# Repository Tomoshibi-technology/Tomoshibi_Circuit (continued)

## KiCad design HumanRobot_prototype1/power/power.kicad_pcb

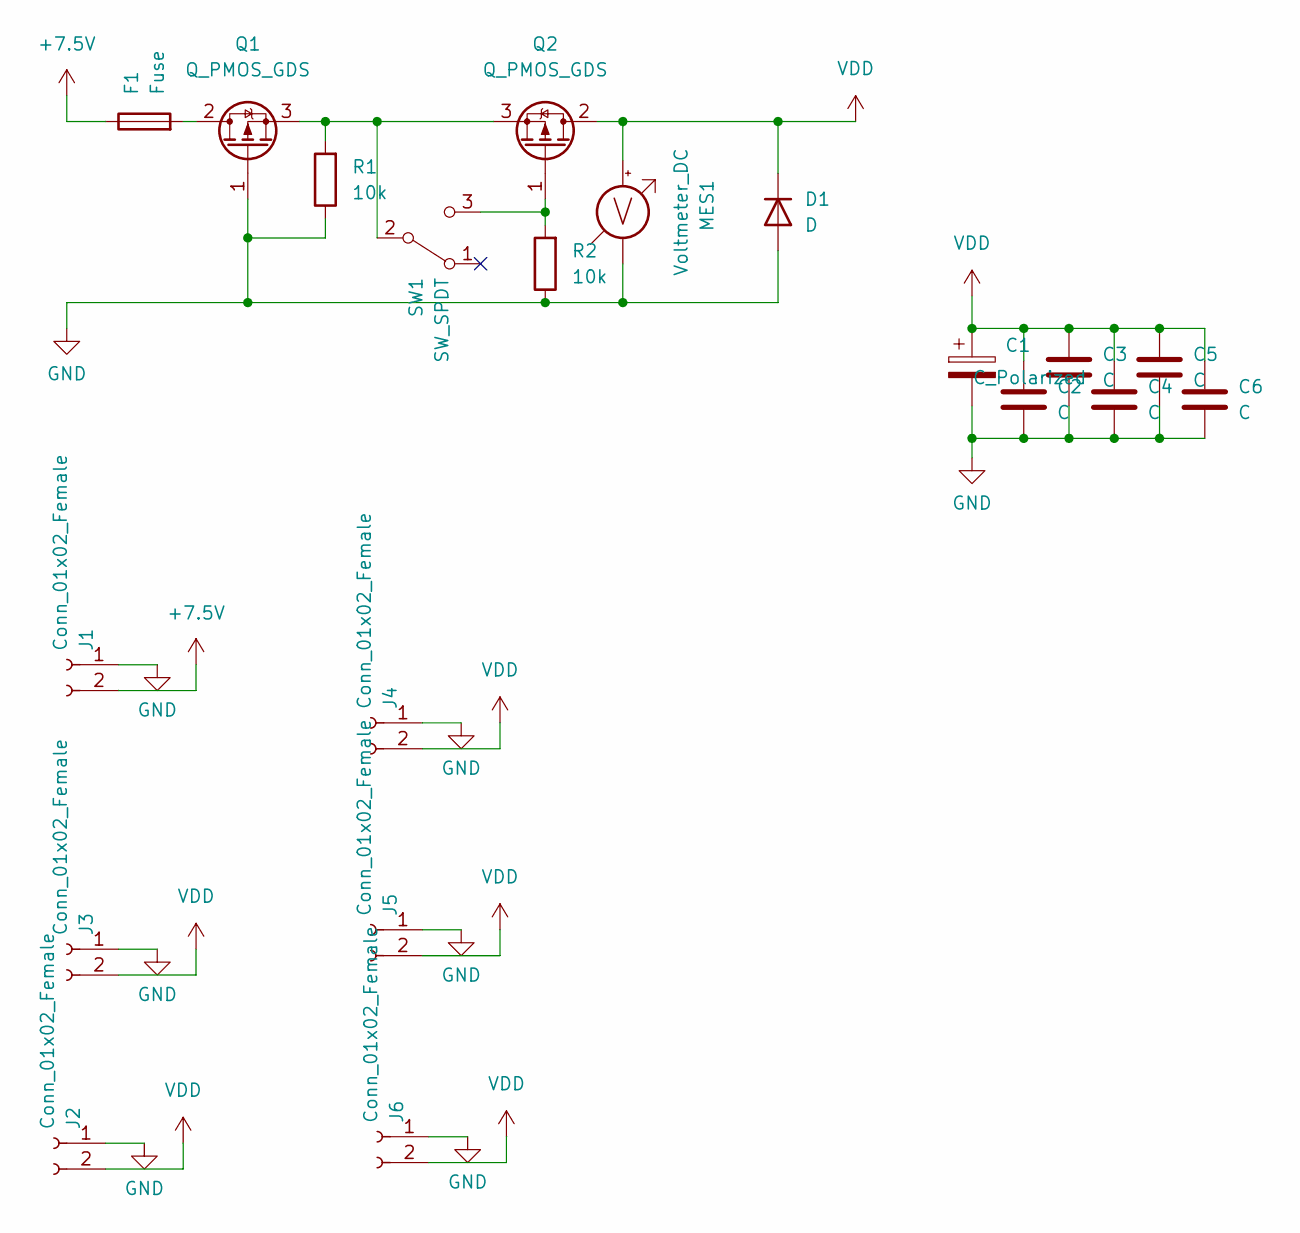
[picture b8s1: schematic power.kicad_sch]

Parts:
C1: C_Polarized; C_Elec_8x10.2
C2, C3, C4, C5, C6: C; C_0603_1608Metric_Pad1.08x0.95mm_HandSolder
D1: D; D_SOD-123
F1: Fuse; FUC_03A
J1: Conn_01x02_Female; AMASS_XT60PW-M_1x02_P7.20mm_Horizontal
J2, J3, J4, J5, J6: Conn_01x02_Female; AMASS_XT30PW-M_1x02_P2.50mm_Horizontal
MES1: Voltmeter_DC; SuperSmallVoltmeter_twoline
Q1, Q2: Q_PMOS_GDS; TO-252-3_TabPin2
R1, R2: 10k; R_0603_1608Metric_Pad0.98x0.95mm_HandSolder
SW1: SW_SPDT; 3P_SPDT_5Pin_ToggleSwitch

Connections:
+7.5V: F1.1, J1.2
GND: C1.2, C2.2, C3.2, C4.2, C5.2, C6.2, D1.2 (A), J1.1, J2.1, J3.1, J4.1, J5.1, J6.1, MES1.1 (-), Q1.1 (G), R1.1, R2.1
unnamed: F1.2, Q1.2 (D)
unnamed: Q1.3 (S), Q2.3 (S), R1.2, SW1.2 (B)
unnamed: Q2.1 (G), R2.2, SW1.3 (C)
VDD: C1.1, C2.1, C3.1, C4.1, C5.1, C6.1, D1.1 (K), J2.2, J3.2, J4.2, J5.2, J6.2, MES1.2 (+), Q2.2 (D)

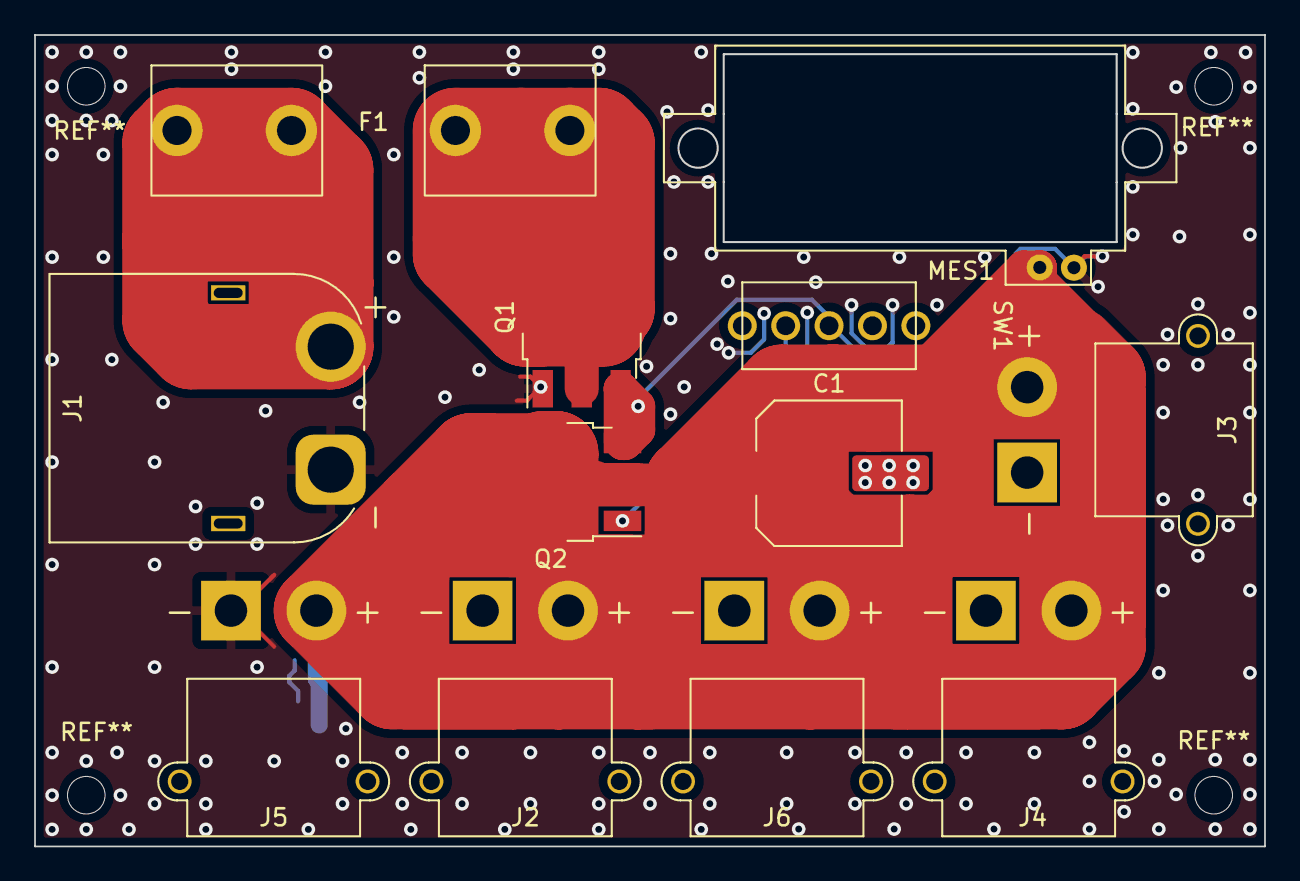
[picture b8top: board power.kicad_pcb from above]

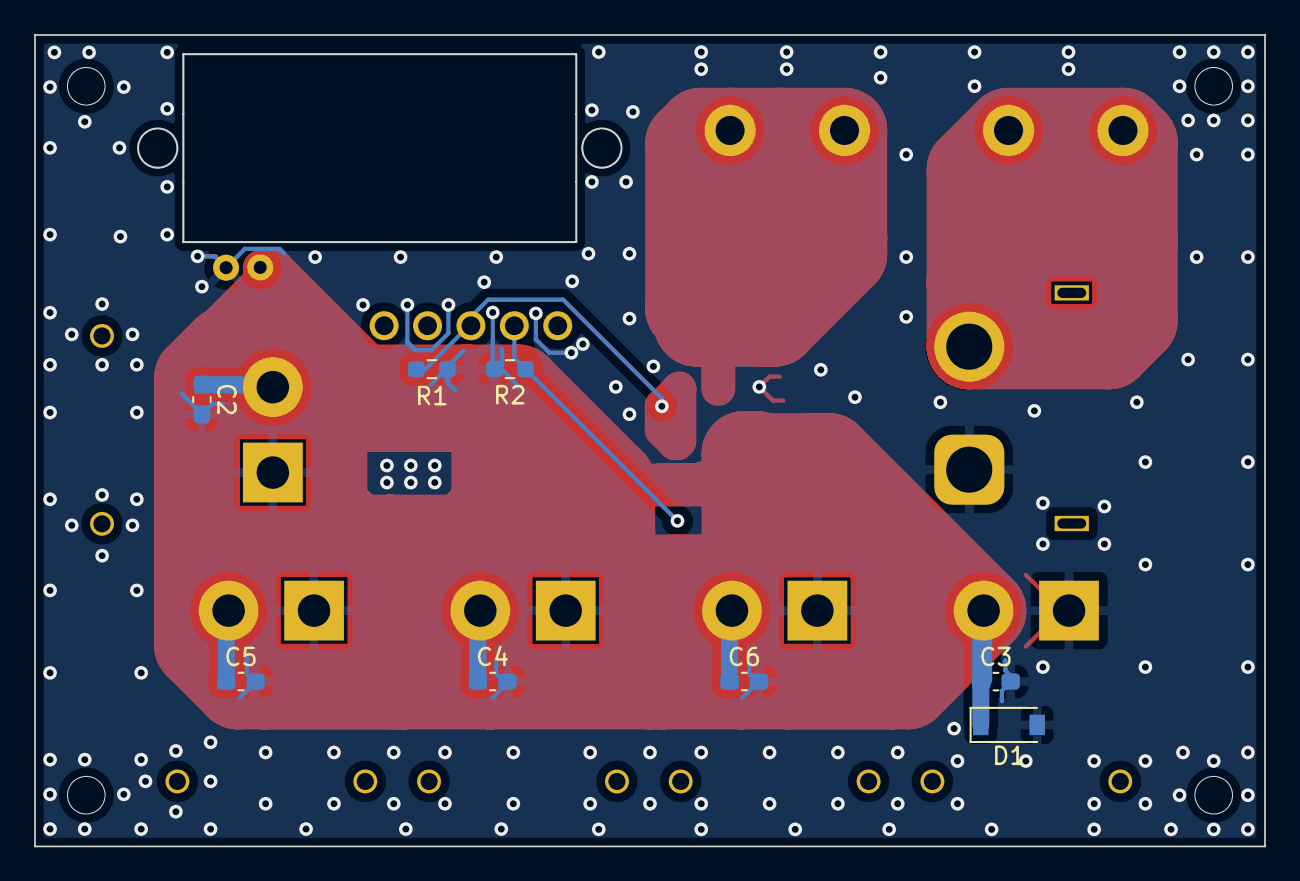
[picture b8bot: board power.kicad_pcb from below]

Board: 2 copper layers, 72.0 x 47.5 mm, 20 parts (8 on the bottom side), 6 nets.

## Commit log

2023-12-25 HelloWorld
2023-12-25 KiCad開発場所移行
2023-12-25 階層変更
2023-12-25 偏光板の基板のプロジェクト
2024-01-23 ピン表追加
2024-01-24 C0のピン表だよ
2024-01-25 エンコーダー基板回路図
2024-02-08 昔作ったやつをマージしておこう
2024-04-28 でこでこしさく
2024-11-09 BLDCMD
2024-11-14 かんせい
2024-11-15 発注後修正1
2024-11-15 とくになにもなし
2024-11-15 gitignore追加
2025-02-06 MDのPDF出力
2025-02-09 パス変更
2025-02-24 ちょっと修正
2025-02-25 また修正
